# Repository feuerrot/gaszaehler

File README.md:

# Gaszählersensor

Dieses Projekt dient dazu, einen über Doppelader angeschlossenen Sensor am
Gaszähler an einen S0-Eingang anzubinden

Der Gaszähler hat in der 6 der dritten Nachkommarstelle eine reflektierende
Scheibe, was es ermöglicht, den Gasverbrauch auf jeweils 1L genau zu
messen.

Da bis zum Gaszähler nur eine Doppelader liegt, schaltet der CNY-70 über
einen Vorwiderstand einen Transistor, wodurch mehr Strom verbraucht wird.
Diese Stromdifferenz wird am anderen Ende der Doppelader dann in ein
binäres Signal übertragen und steht über einen Optokoppler potentialfrei
zur Verfügung.

## Schaltplan

### Sensor

### Konverter

### Beides

## Layout

### Sensor

### Konverter

### Beides

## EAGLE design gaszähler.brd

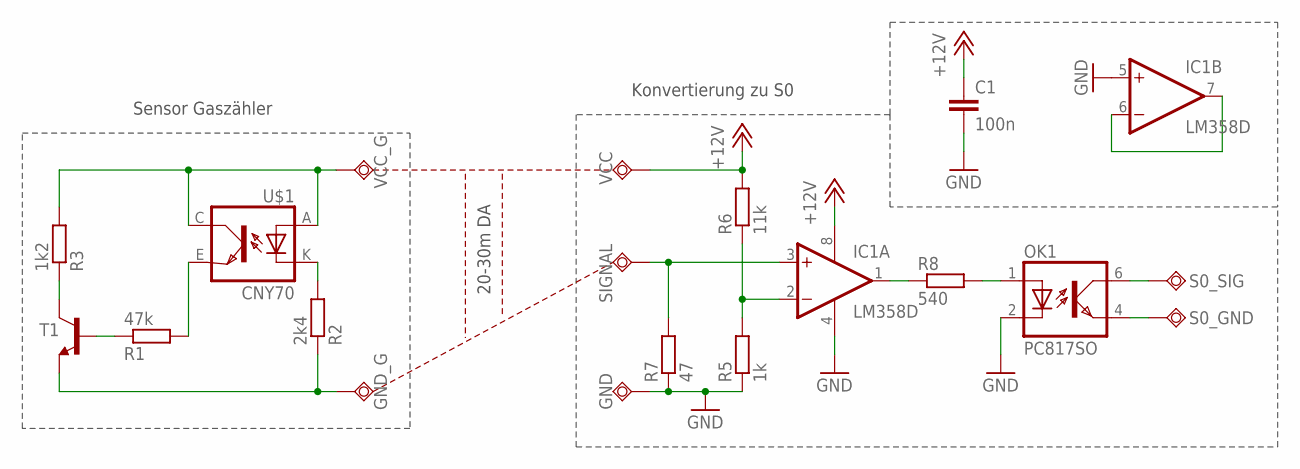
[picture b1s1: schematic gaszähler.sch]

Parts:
C1: 100n; C0805
GND: TPSQTP20SQ; TP20SQ
GND_G: TPSQTP20SQ; TP20SQ
IC1: LM358D; SO08
OK1: PC817SO; SO4
R1: 47k; R0805
R2: 2k4; R0805
R3: 1k2; R0805
R5: 1k; M0805
R6: 11k; M0805
R7: 47; M0805
R8: 540; M0805
S0_GND, S0_SIG: TPSQTP20SQ; TP20SQ
SIGNAL: TPSQTP20SQ; TP20SQ
T1: -NPN-SOT23-EBC; SOT23-EBC
U$1: CNY70; 4
VCC: TPSQTP20SQ; TP20SQ
VCC_G: TPSQTP20SQ; TP20SQ

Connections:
+12V: C1.1, IC1.8 (V+), R6.2, VCC.TP
GND: C1.2, GND.TP, IC1.4 (V-), IC1.5 (+IN), OK1.2 (C), R5.1, R7.1
GND_G: GND_G.TP, R2.1, T1.E
unnamed: IC1.2 (-IN), R5.2, R6.1
unnamed: R2.2, U$1.K (C)
unnamed: R1.2, U$1.E (EMI)
unnamed: IC1.3 (+IN), R7.2, SIGNAL.TP
unnamed: R1.1, T1.B
unnamed: R3.1, T1.C
unnamed: OK1.6 (COL), S0_SIG.TP
unnamed: IC1.1 (OUT), R8.1
unnamed: OK1.4 (EMIT), S0_GND.TP
unnamed: OK1.1 (A), R8.2
unnamed: IC1.6 (-IN), IC1.7 (OUT)
unnamed: R3.2, U$1.A, U$1.C (COL), VCC_G.TP

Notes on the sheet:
20-30m DA
Sensor Gaszähler
Konvertierung zu S0

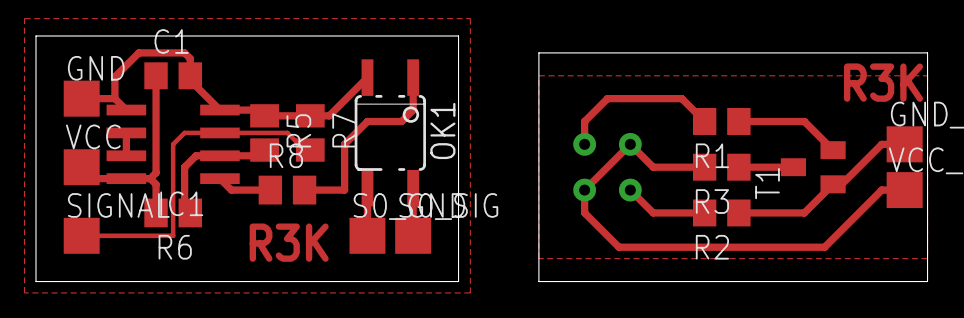
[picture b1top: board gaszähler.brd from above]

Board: 2 copper layers, 49.5 x 13.6 mm, 19 parts (1 on the bottom side), 15 nets.

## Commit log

2014-04-14 adding images
2014-04-14 Readme + Bilder der zwei Teile
2014-04-14 renaming file
2014-04-14 Beschreibung umformuliert und Bilder den kompletten Schaltplan hinzugefügt
